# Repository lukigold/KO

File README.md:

# KO — Keyboard Organization

A premium, slim, wireless keyboard for competitive gaming and creative work, built as a **platform**:
one fixed core board, generated switch boards from 40 % to full size, and magnetic hot-pluggable
modules on all four sides, including force-feedback knobs. Open hardware, Rust firmware.

> **Status:** Phase 0 – requirements frozen as draft v0.1 (2026-11-15). No hardware or code yet.
> **Owner:** the repository owner (personal project, 1–3 units, then published as open source).

---

## How to read this repo

You never need more than these four documents for any task:

1. **This README** – the goal, the architecture, the top-level requirements and the roadmap.
2. **[AGENTS.md](AGENTS.md)** – the working rules for every contributor, human or AI.
3. **The contract for your subsystem** in [`docs/contracts/`](docs/contracts/) – what it must do and how it connects to its neighbours.
4. **[docs/decisions.md](docs/decisions.md)** – why things are the way they are, plus the list of open items.

Contracts follow *design by contract*: every interface states what the provider **guarantees**, what
the consumer must **ensure** (preconditions) and what must **always stay true** (invariants).
Every requirement has a permanent ID, a phase and a verification method.

---

## The product

```
            ┌───────────── Top module: 3 FOC knobs + programmable keys ─────────────┐
            └───────┬──────────── bridges over the two USB-C plugs ────────────┬────┘
┌───────┐┌───────┐┌─┴───────────────────────────────────────────────────────────┴─┐┌──────────┐
│ Macro ││ Macro ││                                                               ││          │
│  1×6  ││  1×6  ││                 KO main keyboard · 75 % · ISO-CH              ││  Numpad  │
│       ││       ││                                                               ││          │
└───────┘└───────┘└───────────────────────────────────────────────────────────────┘└──────────┘
   ← side modules chain left and right          side modules chain left and right →
            ┌──────────────── Front module: wrist rest / power (later) ──────────────┐
            └────────────────────────────────────────────────────────────────────────┘
```

- **Main keyboard:** 75 %, one piece, low profile (~20 mm including keycaps, ~2° built-in tilt),
  CNC aluminium in dark creamy warm silver, per-key RGB, no status LEDs.
- **Connections:** USB-C (any time), 2.4 GHz with its own USB-C dongle for gaming (1,000 Hz),
  Bluetooth for Mac and iOS. Switches between them automatically.
- **Two identical USB-C ports** on the back edge: whichever one sees a computer is the host port,
  the other becomes a small hub port (mouse dongle, USB stick) while the keyboard is wired.
- **Modules** snap on with magnets on all four sides and can be plugged in while running.
  Left and right modules chain (e.g. three 1×6 macro columns plus a numpad).
- **Knob module:** three small force-feedback knobs (smooth, "thocky", music-following),
  profiles switch per application.

### Architecture

```
 Host (Mac/PC) ═USB-C═╗                                       ┌─ 2.4 GHz ── KO dongle ══USB══ Windows PC
                      ║                                       │
   [USB-C A]──┐   role logic   ┌──────────── 7-port USB 2.0 HS hub ───────────┐
   [USB-C B]──┴── + data mux ──┤  ├─ nRF52840 radio module (MCU) ── BLE ── Mac / iOS
                               │  ├─ accessory USB-C port (≤ 500 mA)
                               │  └─ USB lane → each of the 4 module sides
                               └──────────────────────────────────────────────┘
   nRF52840 ══ size-independent connector ══ Switch board (sockets, RGB driver, descriptor EEPROM)
   nRF52840 ══ module bus + 5 V power ══════ 4 module sides (magnets, 6 contacts)
   Flat LiPo ── charger / power path / fuel gauge ── system rails
```

| Subsystem | What it is | Contract | ID prefix |
|---|---|---|---|
| Core board | Fixed "brain": radio MCU, battery, USB ports and hub, module ports | [core-board.md](docs/contracts/core-board.md) | `CORE` |
| Switch board | Generated board: MX + Choc hot-swap sockets, RGB, owns the core↔switch interface | [switch-board.md](docs/contracts/switch-board.md) | `SWB` |
| Module interface | Open spec: magnets, contacts, power, bus, chaining, module catalog | [module-interface.md](docs/contracts/module-interface.md) | `MOD` |
| Wireless | Bluetooth, 2.4 GHz link, dongle, automatic switching | [wireless.md](docs/contracts/wireless.md) | `RF` |
| Firmware | Keyboard firmware (Rust, RMK-based) | [firmware.md](docs/contracts/firmware.md) | `FW` |
| Knob module | Top module with three FOC haptic knobs | [knob-module.md](docs/contracts/knob-module.md) | `KNOB` |
| Host app | Desktop app (Tauri) and host protocol | [host-app.md](docs/contracts/host-app.md) | `APP` |
| Mechanical | Industrial design, case, acoustics, CAD workflow | [mechanical.md](docs/contracts/mechanical.md) | `MECH` |
| Generator | Layout → complete orderable keyboard package | [generator.md](docs/contracts/generator.md) | `GEN` |

---

## Principles (in priority order)

1. **Reliable and simple beats feature-rich.** Every feature must survive daily use for years.
2. **Stable interfaces beat clever implementations.** Contracts are designed to outlive any single board revision.
3. **Performance where you feel it:** typing latency, wireless stability, knob haptics.
4. **Low power by default:** anything power-hungry is off on battery unless the user asks for it.
5. **Everything scripted and reproducible:** PCBs, cases and firmware are generated or built from text files, so agents can work on them.
6. **Open:** share-alike for the product, permissive for the module spec so anyone can build modules.

---

## Top-level requirements

Detailed requirements live in the contracts. These are the ones the whole project is judged by.
Verification: **T** test · **M** measurement · **I** inspection · **A** analysis · **D** demonstration.

| ID | Requirement | Phase | Verify |
|---|---|---|---|
| ~~SYS-01~~ | ~~The main keyboard shall be a one-piece 75 % layout; the owner's build is ISO-CH, and ANSI/ISO variants shall come from the generator.~~ Superseded by SYS-15 (D-57). | P1 | I |
| SYS-02 | Height including keycaps shall be ≤ 18 mm at the front and ≤ 22 mm at the back (goal: 20 mm), with a built-in tilt of about 2° and no fold-out feet. | P6 | M |
| SYS-03 | In basic mode (RGB off, no powered modules) the battery shall last ≥ 4 weeks at 8 h/day of use over 2.4 GHz or Bluetooth. | P2 | M + A |
| SYS-04 | The keyboard shall connect over USB-C (any time, battery or not), 2.4 GHz via the KO dongle, and Bluetooth (Mac/iOS), and choose automatically. | P2 | T |
| SYS-05 | Report rate shall be 1,000 Hz over USB and 2.4 GHz; key-to-host latency ≤ 2 ms wired and ≤ 3 ms over 2.4 GHz (p99). | P2 | M |
| ~~SYS-06~~ | ~~Any MX-style or Kailh Choc v1/v2 switch shall fit the v1 switch board without soldering.~~ Superseded by SYS-16 (D-57). | P1 | T |
| SYS-07 | Two identical USB-C ports: either can be the host/charging port; the other is an accessory port (≤ 500 mA) that works while the keyboard is wired. | P2 | T |
| SYS-08 | Modules shall attach magnetically on all four sides and be hot-pluggable; side modules shall chain left and right; the interface spec shall be public. | P3 | T |
| SYS-09 | The top module shall provide three force-feedback knobs whose behaviour switches per application. | P4 | D |
| SYS-10 | Per-key RGB: on with USB power, off on battery by default. No dedicated status LEDs; the keys are the indicators. | P1 | T |
| SYS-11 | Supported hosts: macOS, Windows, iOS (Bluetooth). Each connection remembers its own keymap / OS mode. | P2 | T |
| SYS-12 | Firmware in Rust; configurable without reflashing (Vial in P1–P2, KO app from P5). | P1 | D |
| SYS-13 | All boards and cases shall be orderable at JLCPCB/PCBWay (PCB, assembly, CNC) and repairable by hand. | P1 | I |
| SYS-14 | Battery and all external contacts shall be protected: LiPo protection, current limits, ESD protection. | P1 | T |
| SYS-15 | The main keyboard shall be one piece in any size the layout builder offers; the switch board is generated from the builder's KO layout file. The owner's first build is 65 % ISO-CH. | P1 | I |
| SYS-16 | Any Kailh Choc v1 or v2 switch shall fit the v1 switch board without soldering (hot-swap), with per-key RGB under every key. | P1 | T |
| SYS-15 | Total prototyping spend shall stay around CHF 2,000. | all | A |
| SYS-16 | License: GPL-3.0-or-later (software), CERN-OHL-S-2.0 (hardware), CC-BY-4.0 + MIT/Apache-2.0 (module spec and its reference code). | P0 | I |

---

## Roadmap

Phases overlap where dependencies allow (e.g. the app can start once the host protocol exists).
Each phase ends with its exit criteria verified and documented.

| Phase | Goal | Main deliverables | Exit criteria |
|---|---|---|---|
| **P0** Foundations | Ready to build | Repo + contracts (this), pinned toolchains, CI skeleton; nRF52840 dev kit, debug probe, Nordic PPK2, 3–4 candidate knob motors bought; RMK + Vial running on the dev kit with a hand-wired test matrix; small-motor comparison on a new 5 V knob test jig (TMC6300 driver, MT6701 sensor) | Firmware flashes, logs and types on the dev kit; knob motor chosen (KNOB-001) |
| **P1** Core keyboard rev A | A usable keyboard | Core board rev A; generated 75 % ISO-CH switch board rev A; 3D-printed case; USB + Bluetooth + Vial; battery and charging; power measured | Daily-usable wired/Bluetooth keyboard; SYS-03 projected from measurements |
| **P2** Wireless and ports | Gaming-grade wireless | Dongle hardware and firmware; encrypted 1 kHz 2.4 GHz link; automatic switching; per-connection keymaps; gaming mode, SOCD; hub and identical ports; core board rev B | SYS-03, SYS-04, SYS-05, SYS-07 verified |
| **P3** Module system | Modules work | Module interface implemented (detection, power, bus, chaining, USB lane); 1×6 macro module; numpad | 3 macro modules + numpad hot-plugged 100× on either side without a fault |
| **P4** Knob module | Haptics | Top module with 3 knobs; Rust FOC firmware; smooth, detent and music profiles; battery modes | Feel matches the owner's reference profiles; power targets met |
| **P5** KO app | Own software | Tauri app replaces Vial: keymaps, macros, lighting, per-app profiles, knob profiles, music knob, notices, updates | All P5 `APP` requirements pass on macOS and Windows |
| **P6** Final design | The premium build | Owner-refined Fusion design → CNC aluminium; acoustics; final board revisions | SYS-02 and finish approved by the owner |
| **P7** Generator | The platform | Local program producing complete packages from 40 % to full size, ANSI/ISO | 3 sizes generated, DRC-clean; one ordered and built |

**Backlog (later, not scheduled):** 8 kHz core board (nRF54LM20), Hall-effect switch board, MX top case,
wireless firmware updates, screen-edge switching between Mac and PC, haptic actuator in the keyboard body,
touch strip / motorized slider modules, screen modules over the USB lane, front power module,
horizontal haptic roller, generator website, Wi-Fi storage module.

---

## Repository layout (target)

```
docs/          contracts/, decisions.md        ← the source of truth
               design/                          ← how contracts are implemented
hardware/      core/, switchboard/ (generated), dongle/, modules/<name>/,
               tools/ (kisch schematic generator, JLCPCB part lookup)
firmware/      Rust workspace: keyboard, dongle, knob-module, side-module,
               ko-protocol, ko-module-bus (shared crates)
app/           Tauri desktop app (macOS, Windows)
generator/     Python: layout → PCB + plate + case package
mechanical/    build123d case skeleton, STEP exports, Fusion handover
tools/         test rigs (latency, power), scripts
LICENSES/      full license texts
```

Only `docs/`, `hardware/` (core board rev A, tools), `generator/` (layout builder page, KO layout file schema and example) and `LICENSES/` exist today; the rest is created in the phase that needs it.

## License

See [LICENSE.md](LICENSE.md). In short: the product is share-alike (GPL-3.0-or-later,
CERN-OHL-S-2.0), the module interface spec and its reference code are permissive
(CC-BY-4.0, MIT/Apache-2.0) so anyone can build KO modules.

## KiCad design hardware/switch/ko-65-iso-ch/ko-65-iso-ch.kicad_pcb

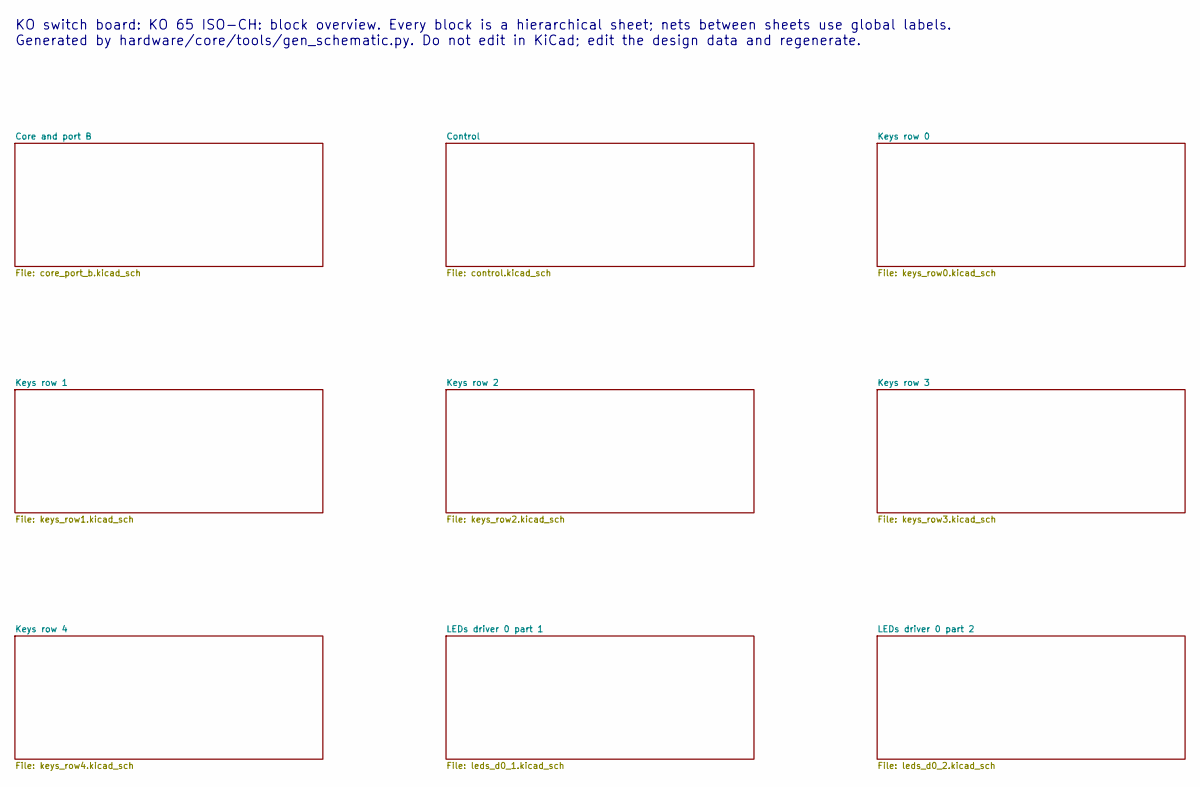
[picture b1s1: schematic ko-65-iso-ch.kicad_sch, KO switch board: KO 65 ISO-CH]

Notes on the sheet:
KO switch board: KO 65 ISO-CH: block overview. Every block is a hierarchical sheet; nets between sheets use global labels. Generated by hardware/core/tools/gen_schematic.py. Do not edit in KiCad; edit the design data and regenerate.

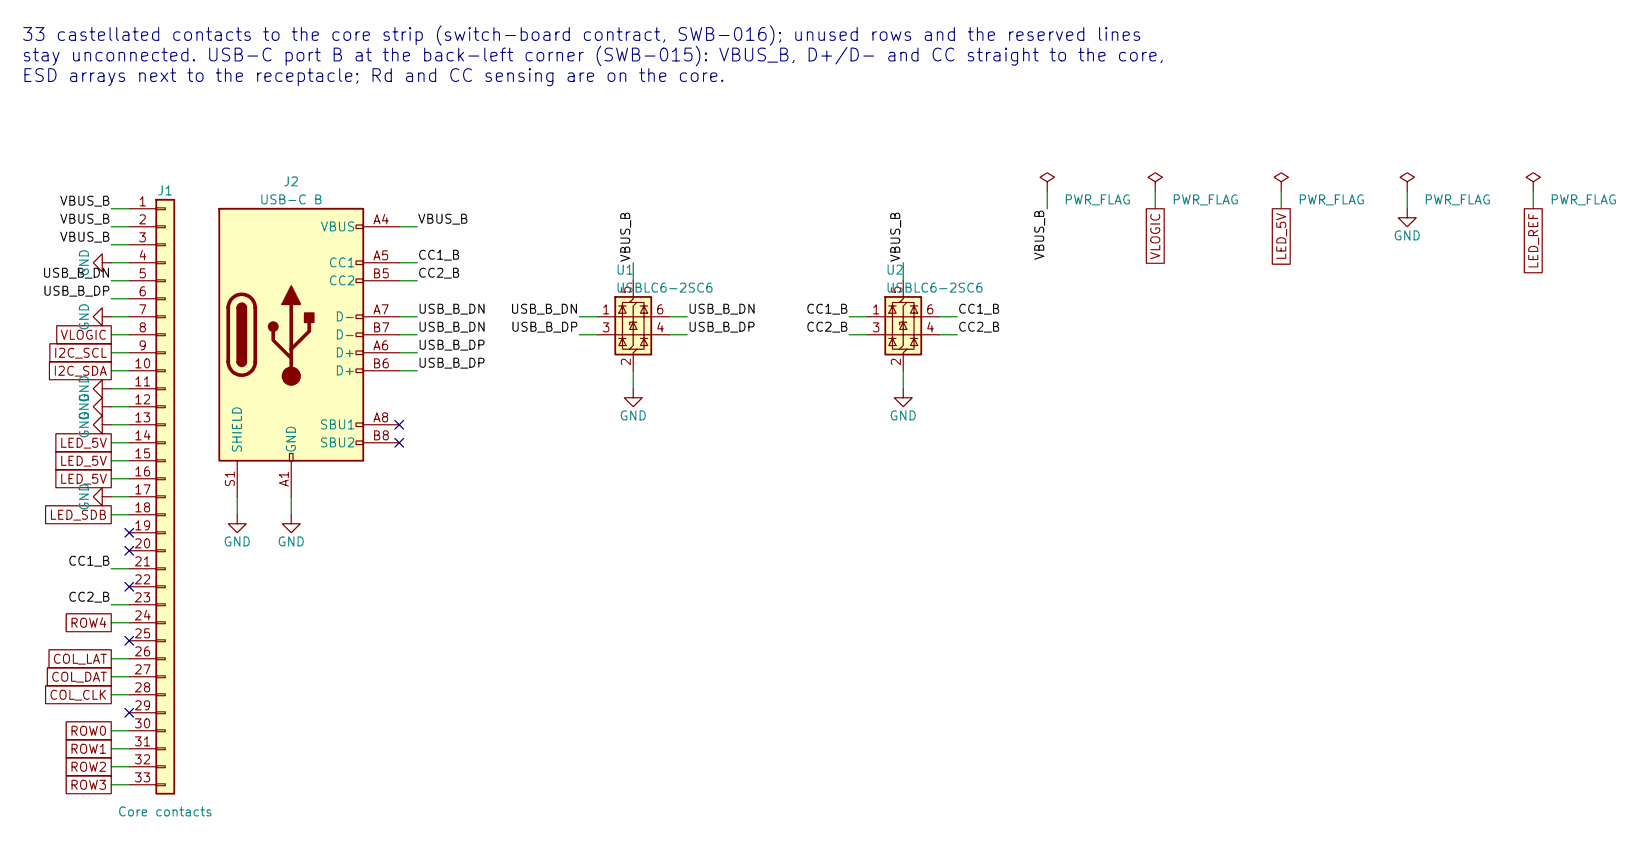
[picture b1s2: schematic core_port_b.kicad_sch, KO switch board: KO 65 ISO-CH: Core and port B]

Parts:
J1: Core contacts; Castellated_1x33_P2.00mm_Edge_Right_1-17_18-33
J2: USB-C B; USB_C_Receptacle_HX_TYPE-C-16P_L10.0; MPN HX TYPE-C 16P L10.0; LCSC C41427495
U1, U2: USBLC6-2SC6; SOT-23-6; MPN USBLC6-2SC6; LCSC C5261088

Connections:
/Core and port B/CC1_B: J1.21, J2.A5 (CC1), U2.1 (I/O1), U2.6 (I/O1)
/Core and port B/CC2_B: J1.23, J2.B5 (CC2), U2.3 (I/O2), U2.4 (I/O2)
/Core and port B/USB_B_DN: J1.5, J2.A7 (D-), J2.B7 (D-), U1.1 (I/O1), U1.6 (I/O1)
/Core and port B/USB_B_DP: J1.6, J2.A6 (D+), J2.B6 (D+), U1.3 (I/O2), U1.4 (I/O2)
/Core and port B/VBUS_B: J1.1, J1.2, J1.3, J2.A4 (VBUS), J2.A9 (VBUS), J2.B4 (VBUS), J2.B9 (VBUS), U1.5 (VBUS), U2.5 (VBUS)
COL_CLK: J1.28; also elsewhere on the board
COL_DAT: J1.27; also elsewhere on the board
COL_LAT: J1.26; also elsewhere on the board
GND: J1.4, J1.7, J1.11, J1.12, J1.13, J1.17, J2.A1 (GND), J2.A12 (GND), J2.B1 (GND), J2.B12 (GND), J2.S1 (SHIELD), U1.2 (GND), U2.2 (GND); also elsewhere on the board
I2C_SCL: J1.9; also elsewhere on the board
I2C_SDA: J1.10; also elsewhere on the board
LED_5V: J1.14, J1.15, J1.16; also elsewhere on the board
LED_SDB: J1.18; also elsewhere on the board
ROW0: J1.30; also elsewhere on the board
ROW1: J1.31; also elsewhere on the board
ROW2: J1.32; also elsewhere on the board
ROW3: J1.33; also elsewhere on the board
ROW4: J1.24; also elsewhere on the board
VLOGIC: J1.8; also elsewhere on the board

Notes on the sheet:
33 castellated contacts to the core strip (switch-board contract, SWB-016); unused rows and the reserved lines stay unconnected. USB-C port B at the back-left corner (SWB-015): VBUS_B, D+/D- and CC straight to the core, ESD arrays next to the receptacle; Rd and CC sensing are on the core.

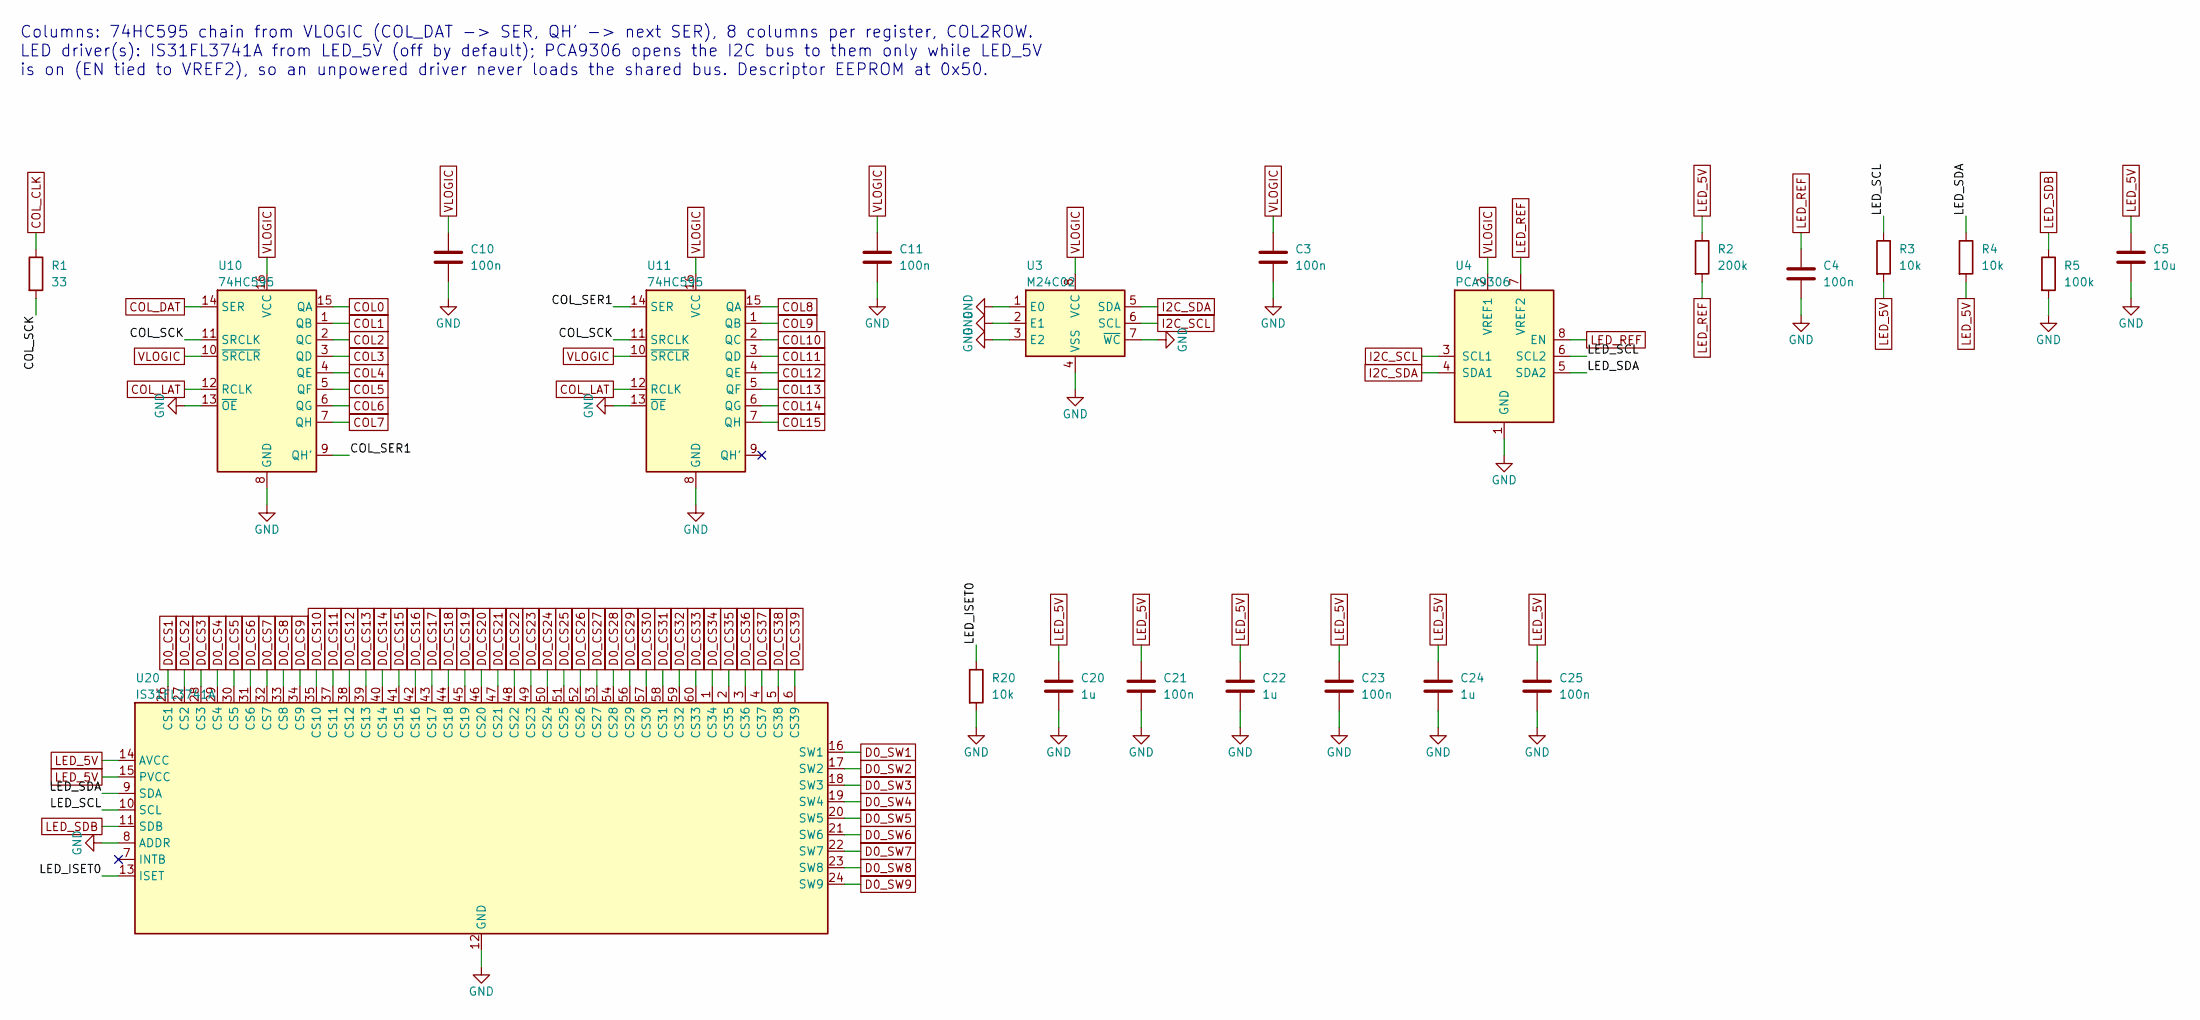
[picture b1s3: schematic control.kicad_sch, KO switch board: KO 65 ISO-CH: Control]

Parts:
C3, C4, C10, C11, C21, C23, C25: 100n; C_0402_1005Metric; MPN CL05B104KO5NNNC; LCSC C1525
C5: 10u; C_0805_2012Metric; MPN CL21A106KAYNNNE; LCSC C15850
C20, C22, C24: 1u; C_0402_1005Metric; MPN CL05A105KA5NQNC; LCSC C52923
R1: 33; R_0402_1005Metric; MPN 0402WGF330JTCE; LCSC C25105
R2: 200k; R_0402_1005Metric; MPN 0402WGF2003TCE; LCSC C25764
R3, R4, R20: 10k; R_0402_1005Metric; MPN 0402WGF1002TCE; LCSC C25744
R5: 100k; R_0402_1005Metric; MPN 0402WGF1003TCE; LCSC C25741
U3: M24C02; TSSOP-8_4.4x3mm_P0.65mm; MPN M24C02-WDW6TP; LCSC C283436
U4: PCA9306; VSSOP-8_2.3x2mm_P0.5mm; MPN PCA9306DCUR; LCSC C33196
U10, U11: 74HC595; SOIC-16_3.9x9.9mm_P1.27mm; MPN 74HC595D(BJ); LCSC C431479
U20: IS31FL3741A; Lumissil_QFN-60_7x7mm_P0.4mm_EP5.4mm; MPN IS31FL3741A-QFLS4-TR; LCSC C2940604

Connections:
/Control/COL_SCK: R1.2, U10.11 (SRCLK), U11.11 (SRCLK)
/Control/COL_SER1: U10.9 (QH'), U11.14 (SER)
/Control/LED_ISET0: R20.1, U20.13 (ISET)
/Control/LED_SCL: R3.1, U4.6 (SCL2), U20.10 (SCL)
/Control/LED_SDA: R4.1, U4.5 (SDA2), U20.9 (SDA)
COL0: U10.15 (QA); also elsewhere on the board
COL1: U10.1 (QB); also elsewhere on the board
COL2: U10.2 (QC); also elsewhere on the board
COL3: U10.3 (QD); also elsewhere on the board
COL4: U10.4 (QE); also elsewhere on the board
COL5: U10.5 (QF); also elsewhere on the board
COL6: U10.6 (QG); also elsewhere on the board
COL7: U10.7 (QH); also elsewhere on the board
COL8: U11.15 (QA); also elsewhere on the board
COL9: U11.1 (QB); also elsewhere on the board
COL10: U11.2 (QC); also elsewhere on the board
COL11: U11.3 (QD); also elsewhere on the board
COL12: U11.4 (QE); also elsewhere on the board
COL13: U11.5 (QF); also elsewhere on the board
COL14: U11.6 (QG); also elsewhere on the board
COL15: U11.7 (QH); also elsewhere on the board
COL_CLK: R1.1; also elsewhere on the board
COL_DAT: U10.14 (SER); also elsewhere on the board
COL_LAT: U10.12 (RCLK), U11.12 (RCLK); also elsewhere on the board
D0_CS1: U20.26 (CS1); also elsewhere on the board
D0_CS2: U20.27 (CS2); also elsewhere on the board
D0_CS3: U20.28 (CS3); also elsewhere on the board
D0_CS4: U20.29 (CS4); also elsewhere on the board
D0_CS5: U20.30 (CS5); also elsewhere on the board
D0_CS6: U20.31 (CS6); also elsewhere on the board
D0_CS7: U20.32 (CS7); also elsewhere on the board
D0_CS8: U20.33 (CS8); also elsewhere on the board
D0_CS9: U20.34 (CS9); also elsewhere on the board
D0_CS10: U20.35 (CS10); also elsewhere on the board
D0_CS11: U20.37 (CS11); also elsewhere on the board
D0_CS12: U20.38 (CS12); also elsewhere on the board
D0_CS13: U20.39 (CS13); also elsewhere on the board
D0_CS14: U20.40 (CS14); also elsewhere on the board
D0_CS15: U20.41 (CS15); also elsewhere on the board
D0_CS16: U20.42 (CS16); also elsewhere on the board
D0_CS17: U20.43 (CS17); also elsewhere on the board
D0_CS18: U20.44 (CS18); also elsewhere on the board
D0_CS19: U20.45 (CS19); also elsewhere on the board
D0_CS20: U20.46 (CS20); also elsewhere on the board
D0_CS21: U20.47 (CS21); also elsewhere on the board
D0_CS22: U20.48 (CS22); also elsewhere on the board
D0_CS23: U20.49 (CS23); also elsewhere on the board
D0_CS24: U20.50 (CS24); also elsewhere on the board
D0_CS25: U20.51 (CS25); also elsewhere on the board
D0_CS26: U20.52 (CS26); also elsewhere on the board
D0_CS27: U20.53 (CS27); also elsewhere on the board
D0_CS28: U20.54 (CS28); also elsewhere on the board
D0_CS29: U20.56 (CS29); also elsewhere on the board
D0_CS30: U20.57 (CS30); also elsewhere on the board
D0_CS31: U20.58 (CS31); also elsewhere on the board
D0_CS32: U20.59 (CS32); also elsewhere on the board
D0_CS33: U20.60 (CS33); also elsewhere on the board
D0_CS34: U20.1 (CS34); also elsewhere on the board
D0_CS35: U20.2 (CS35); also elsewhere on the board
D0_CS36: U20.3 (CS36); also elsewhere on the board
D0_CS37: U20.4 (CS37); also elsewhere on the board
D0_CS38: U20.5 (CS38); also elsewhere on the board
D0_CS39: U20.6 (CS39); also elsewhere on the board
D0_SW1: U20.16 (SW1); also elsewhere on the board
D0_SW2: U20.17 (SW2); also elsewhere on the board
D0_SW3: U20.18 (SW3); also elsewhere on the board
D0_SW4: U20.19 (SW4); also elsewhere on the board
D0_SW5: U20.20 (SW5); also elsewhere on the board
D0_SW6: U20.21 (SW6); also elsewhere on the board
D0_SW7: U20.22 (SW7); also elsewhere on the board
D0_SW8: U20.23 (SW8); also elsewhere on the board
D0_SW9: U20.24 (SW9); also elsewhere on the board
GND: C3.2, C4.2, C5.2, C10.2, C11.2, C20.2, C21.2, C22.2, C23.2, C24.2, C25.2, R5.2, R20.2, U3.1 (E0), U3.2 (E1), U3.3 (E2), U3.4 (VSS), U3.7 (~WC), U4.1 (GND), U10.8 (GND), U10.13 (~OE), U11.8 (GND), U11.13 (~OE), U20.8 (ADDR), U20.12 (GND), U20.36 (GND), U20.55 (GND), U20.61 (GND); also elsewhere on the board
I2C_SCL: U3.6 (SCL), U4.3 (SCL1); also elsewhere on the board
I2C_SDA: U3.5 (SDA), U4.4 (SDA1); also elsewhere on the board
LED_5V: C5.1, C20.1, C21.1, C22.1, C23.1, C24.1, C25.1, R2.1, R3.2, R4.2, U20.14 (AVCC), U20.15 (PVCC), U20.25 (PVCC); also elsewhere on the board
LED_REF: C4.1, R2.2, U4.7 (VREF2), U4.8 (EN)
LED_SDB: R5.1, U20.11 (SDB); also elsewhere on the board
VLOGIC: C3.1, C10.1, C11.1, U3.8 (VCC), U4.2 (VREF1), U10.10 (~SRCLR), U10.16 (VCC), U11.10 (~SRCLR), U11.16 (VCC); also elsewhere on the board

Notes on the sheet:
Columns: 74HC595 chain from VLOGIC (COL_DAT -> SER, QH' -> next SER), 8 columns per register, COL2ROW. LED driver(s): IS31FL3741A from LED_5V (off by default); PCA9306 opens the I2C bus to them only while LED_5V is on (EN tied to VREF2), so an unpowered driver never loads the shared bus. Descriptor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

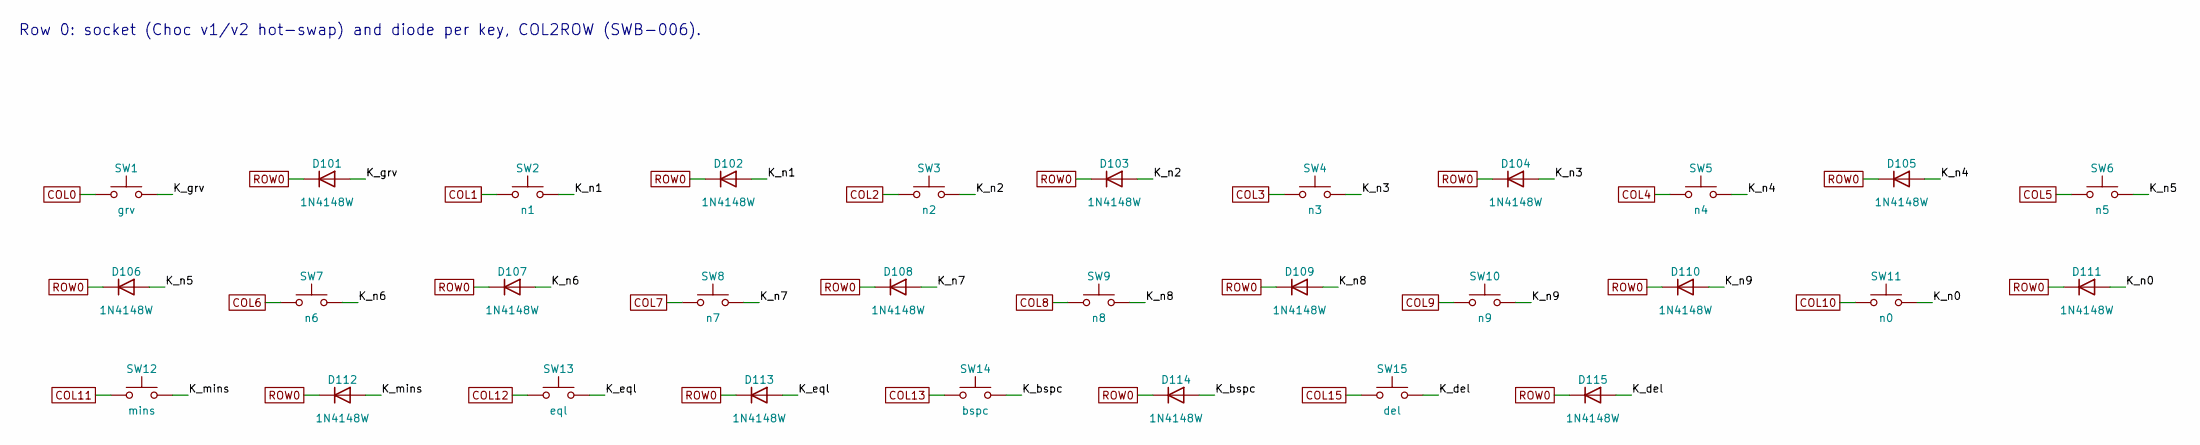
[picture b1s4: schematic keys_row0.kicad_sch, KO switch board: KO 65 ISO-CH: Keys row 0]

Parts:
D101, D102, D103, D104, D105, D106, D107, D108, D109, D110, D111, D112, D113, D114, D115: 1N4148W; D_SOD-123; MPN 1N4148W; LCSC C81598
SW1: grv; Key_Choc_V1V2_Hotswap_CPG1350; MPN Kailh CPG135001S30
SW2: n1; Key_Choc_V1V2_Hotswap_CPG1350; MPN Kailh CPG135001S30
SW3: n2; Key_Choc_V1V2_Hotswap_CPG1350; MPN Kailh CPG135001S30
SW4: n3; Key_Choc_V1V2_Hotswap_CPG1350; MPN Kailh CPG135001S30
SW5: n4; Key_Choc_V1V2_Hotswap_CPG1350; MPN Kailh CPG135001S30
SW6: n5; Key_Choc_V1V2_Hotswap_CPG1350; MPN Kailh CPG135001S30
SW7: n6; Key_Choc_V1V2_Hotswap_CPG1350; MPN Kailh CPG135001S30
SW8: n7; Key_Choc_V1V2_Hotswap_CPG1350; MPN Kailh CPG135001S30
SW9: n8; Key_Choc_V1V2_Hotswap_CPG1350; MPN Kailh CPG135001S30
SW10: n9; Key_Choc_V1V2_Hotswap_CPG1350; MPN Kailh CPG135001S30
SW11: n0; Key_Choc_V1V2_Hotswap_CPG1350; MPN Kailh CPG135001S30
SW12: mins; Key_Choc_V1V2_Hotswap_CPG1350; MPN Kailh CPG135001S30
SW13: eql; Key_Choc_V1V2_Hotswap_CPG1350; MPN Kailh CPG135001S30
SW14: bspc; Key_Choc_V1V2_Hotswap_CPG1350; MPN Kailh CPG135001S30
SW15: del; Key_Choc_V1V2_Hotswap_CPG1350; MPN Kailh CPG135001S30

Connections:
/Keys row 0/K_bspc: D114.2 (A), SW14.2
/Keys row 0/K_del: D115.2 (A), SW15.2
/Keys row 0/K_eql: D113.2 (A), SW13.2
/Keys row 0/K_grv: D101.2 (A), SW1.2
/Keys row 0/K_mins: D112.2 (A), SW12.2
/Keys row 0/K_n0: D111.2 (A), SW11.2
/Keys row 0/K_n1: D102.2 (A), SW2.2
/Keys row 0/K_n2: D103.2 (A), SW3.2
/Keys row 0/K_n3: D104.2 (A), SW4.2
/Keys row 0/K_n4: D105.2 (A), SW5.2
/Keys row 0/K_n5: D106.2 (A), SW6.2
/Keys row 0/K_n6: D107.2 (A), SW7.2
/Keys row 0/K_n7: D108.2 (A), SW8.2
/Keys row 0/K_n8: D109.2 (A), SW9.2
/Keys row 0/K_n9: D110.2 (A), SW10.2
COL0: SW1.1; also elsewhere on the board
COL1: SW2.1; also elsewhere on the board
COL2: SW3.1; also elsewhere on the board
COL3: SW4.1; also elsewhere on the board
COL4: SW5.1; also elsewhere on the board
COL5: SW6.1; also elsewhere on the board
COL6: SW7.1; also elsewhere on the board
COL7: SW8.1; also elsewhere on the board
COL8: SW9.1; also elsewhere on the board
COL9: SW10.1; also elsewhere on the board
COL10: SW11.1; also elsewhere on the board
COL11: SW12.1; also elsewhere on the board
COL12: SW13.1; also elsewhere on the board
COL13: SW14.1; also elsewhere on the board
COL15: SW15.1; also elsewhere on the board
ROW0: D101.1 (K), D102.1 (K), D103.1 (K), D104.1 (K), D105.1 (K), D106.1 (K), D107.1 (K), D108.1 (K), D109.1 (K), D110.1 (K), D111.1 (K), D112.1 (K), D113.1 (K), D114.1 (K), D115.1 (K); also elsewhere on the board

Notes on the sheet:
Row 0: socket (Choc v1/v2 hot-swap) and diode per key, COL2ROW (SWB-006).

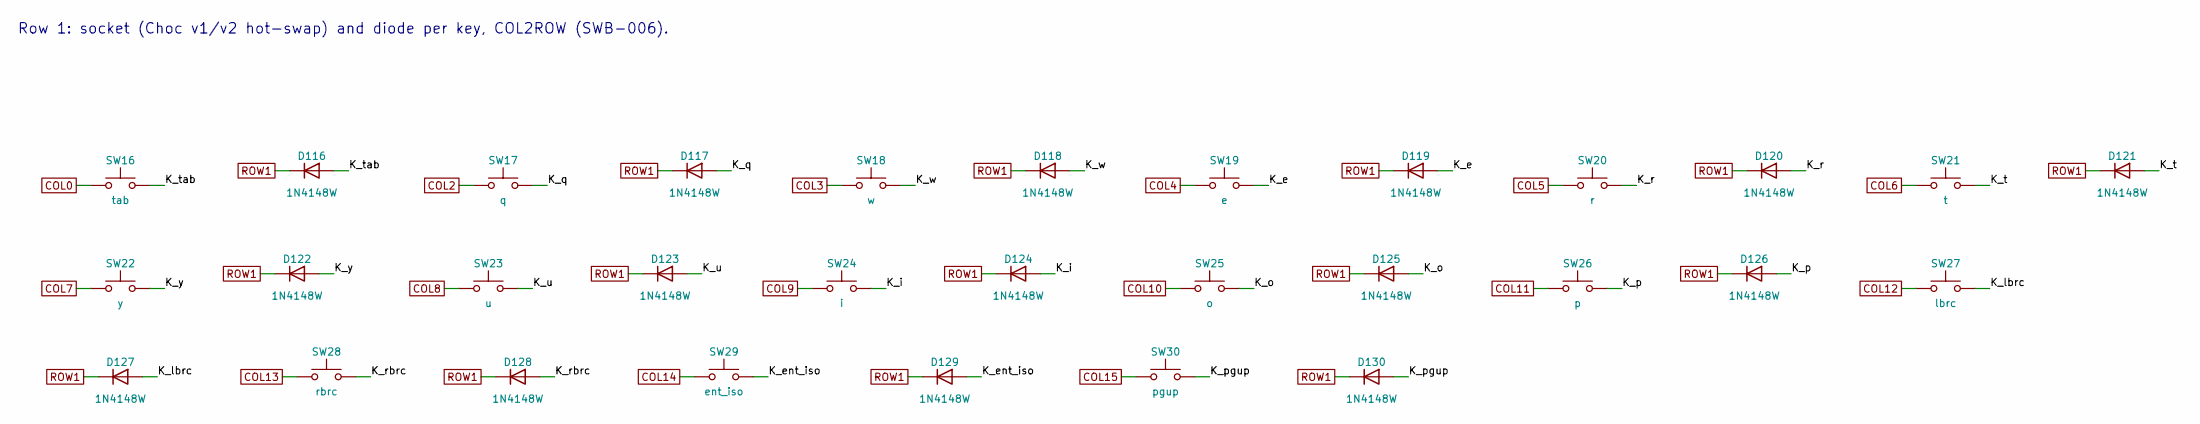
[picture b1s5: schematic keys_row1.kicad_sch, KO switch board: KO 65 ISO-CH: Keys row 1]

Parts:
D116, D117, D118, D119, D120, D121, D122, D123, D124, D125, D126, D127, D128, D129, D130: 1N4148W; D_SOD-123; MPN 1N4148W; LCSC C81598
SW16: tab; Key_Choc_V1V2_Hotswap_CPG1350; MPN Kailh CPG135001S30
SW17: q; Key_Choc_V1V2_Hotswap_CPG1350; MPN Kailh CPG135001S30
SW18: w; Key_Choc_V1V2_Hotswap_CPG1350; MPN Kailh CPG135001S30
SW19: e; Key_Choc_V1V2_Hotswap_CPG1350; MPN Kailh CPG135001S30
SW20: r; Key_Choc_V1V2_Hotswap_CPG1350; MPN Kailh CPG135001S30
SW21: t; Key_Choc_V1V2_Hotswap_CPG1350; MPN Kailh CPG135001S30
SW22: y; Key_Choc_V1V2_Hotswap_CPG1350; MPN Kailh CPG135001S30
SW23: u; Key_Choc_V1V2_Hotswap_CPG1350; MPN Kailh CPG135001S30
SW24: i; Key_Choc_V1V2_Hotswap_CPG1350; MPN Kailh CPG135001S30
SW25: o; Key_Choc_V1V2_Hotswap_CPG1350; MPN Kailh CPG135001S30
SW26: p; Key_Choc_V1V2_Hotswap_CPG1350; MPN Kailh CPG135001S30
SW27: lbrc; Key_Choc_V1V2_Hotswap_CPG1350; MPN Kailh CPG135001S30
SW28: rbrc; Key_Choc_V1V2_Hotswap_CPG1350; MPN Kailh CPG135001S30
SW29: ent_iso; Key_Choc_V1V2_Hotswap_CPG1350; MPN Kailh CPG135001S30
SW30: pgup; Key_Choc_V1V2_Hotswap_CPG1350; MPN Kailh CPG135001S30

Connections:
/Keys row 1/K_e: D119.2 (A), SW19.2
/Keys row 1/K_ent_iso: D129.2 (A), SW29.2
/Keys row 1/K_i: D124.2 (A), SW24.2
/Keys row 1/K_lbrc: D127.2 (A), SW27.2
/Keys row 1/K_o: D125.2 (A), SW25.2
/Keys row 1/K_p: D126.2 (A), SW26.2
/Keys row 1/K_pgup: D130.2 (A), SW30.2
/Keys row 1/K_q: D117.2 (A), SW17.2
/Keys row 1/K_r: D120.2 (A), SW20.2
/Keys row 1/K_rbrc: D128.2 (A), SW28.2
/Keys row 1/K_t: D121.2 (A), SW21.2
/Keys row 1/K_tab: D116.2 (A), SW16.2
/Keys row 1/K_u: D123.2 (A), SW23.2
/Keys row 1/K_w: D118.2 (A), SW18.2
/Keys row 1/K_y: D122.2 (A), SW22.2
COL0: SW16.1; also elsewhere on the board
COL2: SW17.1; also elsewhere on the board
COL3: SW18.1; also elsewhere on the board
COL4: SW19.1; also elsewhere on the board
COL5: SW20.1; also elsewhere on the board
COL6: SW21.1; also elsewhere on the board
COL7: SW22.1; also elsewhere on the board
COL8: SW23.1; also elsewhere on the board
COL9: SW24.1; also elsewhere on the board
COL10: SW25.1; also elsewhere on the board
COL11: SW26.1; also elsewhere on the board
COL12: SW27.1; also elsewhere on the board
COL13: SW28.1; also elsewhere on the board
COL14: SW29.1; also elsewhere on the board
COL15: SW30.1; also elsewhere on the board
ROW1: D116.1 (K), D117.1 (K), D118.1 (K), D119.1 (K), D120.1 (K), D121.1 (K), D122.1 (K), D123.1 (K), D124.1 (K), D125.1 (K), D126.1 (K), D127.1 (K), D128.1 (K), D129.1 (K), D130.1 (K); also elsewhere on the board

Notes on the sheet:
Row 1: socket (Choc v1/v2 hot-swap) and diode per key, COL2ROW (SWB-006).

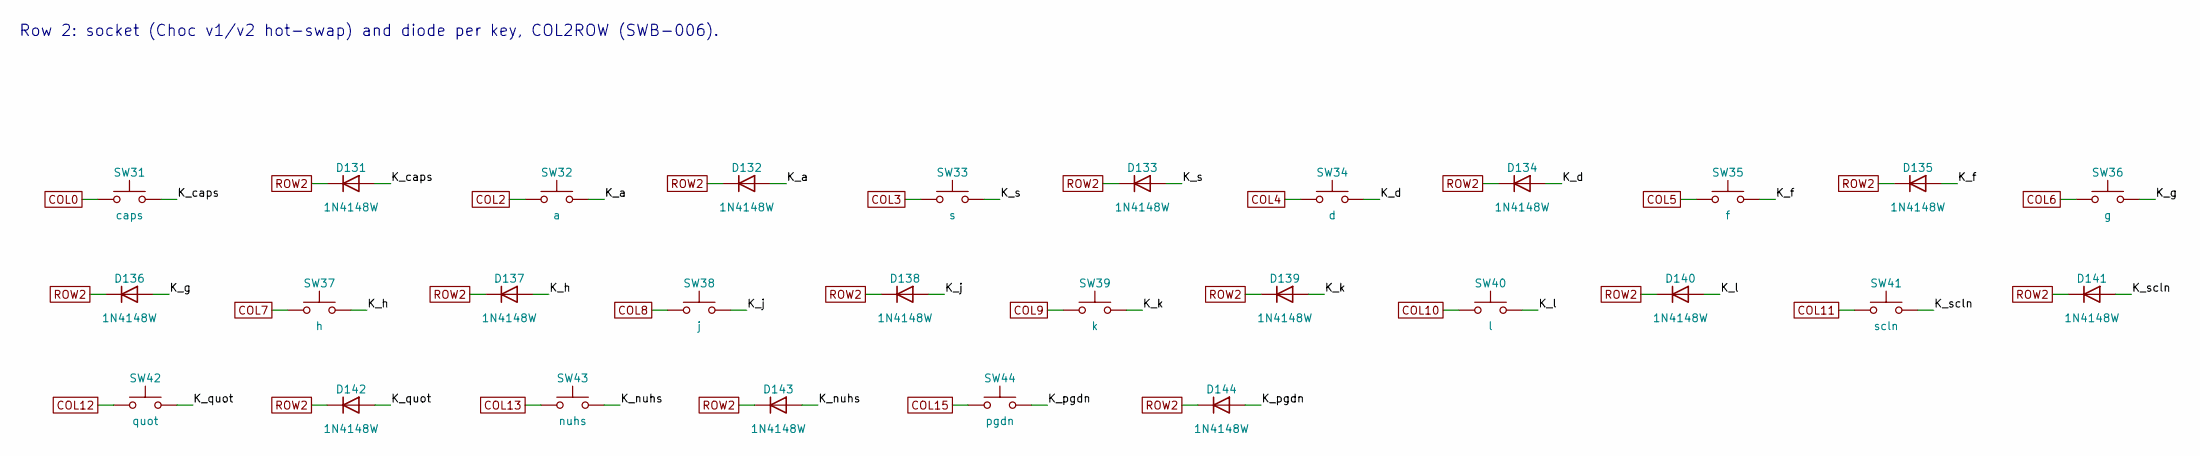
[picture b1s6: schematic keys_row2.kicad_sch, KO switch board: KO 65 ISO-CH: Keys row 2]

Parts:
D131, D132, D133, D134, D135, D136, D137, D138, D139, D140, D141, D142, D143, D144: 1N4148W; D_SOD-123; MPN 1N4148W; LCSC C81598
SW31: caps; Key_Choc_V1V2_Hotswap_CPG1350; MPN Kailh CPG135001S30
SW32: a; Key_Choc_V1V2_Hotswap_CPG1350; MPN Kailh CPG135001S30
SW33: s; Key_Choc_V1V2_Hotswap_CPG1350; MPN Kailh CPG135001S30
SW34: d; Key_Choc_V1V2_Hotswap_CPG1350; MPN Kailh CPG135001S30
SW35: f; Key_Choc_V1V2_Hotswap_CPG1350; MPN Kailh CPG135001S30
SW36: g; Key_Choc_V1V2_Hotswap_CPG1350; MPN Kailh CPG135001S30
SW37: h; Key_Choc_V1V2_Hotswap_CPG1350; MPN Kailh CPG135001S30
SW38: j; Key_Choc_V1V2_Hotswap_CPG1350; MPN Kailh CPG135001S30
SW39: k; Key_Choc_V1V2_Hotswap_CPG1350; MPN Kailh CPG135001S30
SW40: l; Key_Choc_V1V2_Hotswap_CPG1350; MPN Kailh CPG135001S30
SW41: scln; Key_Choc_V1V2_Hotswap_CPG1350; MPN Kailh CPG135001S30
SW42: quot; Key_Choc_V1V2_Hotswap_CPG1350; MPN Kailh CPG135001S30
SW43: nuhs; Key_Choc_V1V2_Hotswap_CPG1350; MPN Kailh CPG135001S30
SW44: pgdn; Key_Choc_V1V2_Hotswap_CPG1350; MPN Kailh CPG135001S30

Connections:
/Keys row 2/K_a: D132.2 (A), SW32.2
/Keys row 2/K_caps: D131.2 (A), SW31.2
/Keys row 2/K_d: D134.2 (A), SW34.2
/Keys row 2/K_f: D135.2 (A), SW35.2
/Keys row 2/K_g: D136.2 (A), SW36.2
/Keys row 2/K_h: D137.2 (A), SW37.2
/Keys row 2/K_j: D138.2 (A), SW38.2
/Keys row 2/K_k: D139.2 (A), SW39.2
/Keys row 2/K_l: D140.2 (A), SW40.2
/Keys row 2/K_nuhs: D143.2 (A), SW43.2
/Keys row 2/K_pgdn: D144.2 (A), SW44.2
/Keys row 2/K_quot: D142.2 (A), SW42.2
/Keys row 2/K_s: D133.2 (A), SW33.2
/Keys row 2/K_scln: D141.2 (A), SW41.2
COL0: SW31.1; also elsewhere on the board
COL2: SW32.1; also elsewhere on the board
COL3: SW33.1; also elsewhere on the board
COL4: SW34.1; also elsewhere on the board
COL5: SW35.1; also elsewhere on the board
COL6: SW36.1; also elsewhere on the board
COL7: SW37.1; also elsewhere on the board
COL8: SW38.1; also elsewhere on the board
COL9: SW39.1; also elsewhere on the board
COL10: SW40.1; also elsewhere on the board
COL11: SW41.1; also elsewhere on the board
COL12: SW42.1; also elsewhere on the board
COL13: SW43.1; also elsewhere on the board
COL15: SW44.1; also elsewhere on the board
ROW2: D131.1 (K), D132.1 (K), D133.1 (K), D134.1 (K), D135.1 (K), D136.1 (K), D137.1 (K), D138.1 (K), D139.1 (K), D140.1 (K), D141.1 (K), D142.1 (K), D143.1 (K), D144.1 (K); also elsewhere on the board

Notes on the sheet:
Row 2: socket (Choc v1/v2 hot-swap) and diode per key, COL2ROW (SWB-006).

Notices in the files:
hardware/core/tools/gen_schematic.py:
SPDX-License-Identifier: GPL-3.0-or-later
comments=["SPDX-License-Identifier: CERN-OHL-S-2.0",
hardware/core/tools/route_pcb.py:
autoroute needs Freerouting (GPL-3.0, https://github.com/freerouting/freerouting) and a Java runtime
hardware/core/ko-core.kicad_pcb:
SPDX-License-Identifier: CERN-OHL-S-2.0
